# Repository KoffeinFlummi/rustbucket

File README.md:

rustbucket
==========

Access your car's diagnostics via the OBD2 connector with a BeagleBone Blue and Rust (and maybe some MOSFETs). This was inspired by [Marcelo Sacchetin's post about using the BeagleBone Blue's integrated CAN bus transceiver](https://medium.com/bugbountywriteup/car-hacking-with-python-part-1-data-exfiltration-gps-and-obdii-can-bus-69bc6b101fd1). If you want to read the diagnostics for older vehicles, things are a bit more complicated than that. For older VWs for instance, you will need to talk to the vehicle's K line using the KWP1281 protocol. This requires additional hardware to convert the BeagleBone's 3.3V logic level to 12V.

This was developed on/for the BeagleBone Blue, but the K & L line protocols should be just as usable on a BeagleBone Black. As far as I know, accessing the CAN bus on the Black requires the addition of a CAN transceiver.

<p align="center">
    
</p>

# Disclaimer

Hooking stuff up to your vehicle's OBD2 connector can lead to anything from blown fuses to broken hardware. There are [reports online of attempting to communicate with certain VW airbag controllers via KWP1281 bricking them](https://www.ross-tech.com/vag-com/vw_issues.html). There are also apparently [instances of clearing the fault codes using KWP1281 leading to deployed airbags for certain errors](http://wiki.ross-tech.com/wiki/index.php/01217).

I have tested the software and hardware described here successfully on some vehicles/ECUs (see below). However, **I cannot provide any guarantee that using this will not cause permanent damage to you or your vehicle. Proceed at your own risk. Also, don't fuck with airbags please.**

# Protocols

<p align="center">
    
</p>

| Protocol            | Used Lines         | Implemented | Notes |
|---------------------|--------------------|:-----------:|----------------------------------------------------------------------|
| CAN Bus / ISO 15765 | CAN High & CAN Low | ✓           | Used by almost any modern vehicle. No additional hardware needed; The BB Blue's CAN transceiver can be connected directly to the OBD port's CAN lines. |
| KWP1281             | K Line             | ✓           | Not an official OBD2 protocol, used on older VAG (VW & friends) cars. Returned codes are not official OBD2 DTCs. |
| ISO 9141            | K & L Line         | ✗           | Apparently similar to KWP1281, but an official OBD2 protocol. Not implemented, but technically supported by hardware described below. |
| KWP2000 / ISO 14230 | K & L Line         | (✓)         | Implemented at least partially (K line init only, no fast init). OBD2 commands not implemented, but some VAG specific stuff has been tested (see below). |

There are some more OBD2 protocols, that apparently are mostly used on American vehicles. I have not considered these, and the hardware required seems quite different.

Note that the above is my understanding, this whole field is a giant mess of standards and acronyms.

# Features

- Read Diagnostic Trouble Codes, stored and pending
- Clear Diagnostic Trouble Codes
- Read diagnostic data, current and from freeze frame
- Log diagnostic data to CSV for plotting
- Read and write adaptation values, e.g. to reset the service interval (KWP1281 only, no login functionality _yet_)
- Perform basic settings, such as throttle body alignments (KWP1281 only)

# Tested Vehicles/ECUs

| Vehicle/ECU                  | Protocol | Baud/Bit Rate   | Notes |
|------------------------------|----------|-----------------|-------|
| VW Golf Mk4 (1J), 2001       | KWP1281  | 10400,9600,1200 | All ECUs except ESP and airbag controller. See [script](https://github.com/KoffeinFlummi/rustbucket/blob/master/scan_golf_mk4.sh) and [sample output](https://github.com/KoffeinFlummi/rustbucket/blob/master/scan_golf_mk4_sample.out). |
| VW Golf Mk4 (1J), 2001       | KWP2000  | 10400           | ESP Mk60 controller. Reading & clearing DTCs only. |
| VW Golf Mk7 (AUV), 2014      | CAN      | 500000          | Most things work, but multi-frame messages (VIN, more than 2 DTCs) do not. Might require modifications to flow control messages. |
| ~Renault Zoe (AGVYB0), 2015~ | CAN      | 500000          | CAN bus is active, but does not respond to OBD2 queries. I did not spend much time on this, might require some sort of initialization. |
| Siemens SIMOS2.1B ECU        | KWP1281  | 9600            | [Pinout](https://wiki.obdtuning.de/images/9/99/VAG_Simos2.4.jpg) (also has a 500kbps CAN bus on pins 29 (L) & 31 (H), but this is not used for diagnostics and does not respond to OBD2 queries) |
| Bosch EDC16U34 ECU           | CAN      | 500000          | [Pinout](http://diagprof.com/de/ecu_tipps_und_tricks/vag/motorelektronik/bosch/edc16u34) |

# Compiling & Usage

You can compile this directly on the BeagleBone, but the compilation times can be annoying, so the project is set up for cross-compilation. You will have to add the `armv7-unknown-linux-gnueabihf` target using `rustup` (You'll also need a version of GCC compiled for `arm-linux-gnueabihf` for linking. Consult your OS' package manager.):

```
$ rustup target add armv7-unknown-linux-gnueabihf
$ cargo build --release
```

Then, copy the executable to the BeagleBone.

See `rustbucket -h` for usage.

# Testing

The program contains modes for testing the hardware and simulating a car so you can test your hardware using two BeagleBones instead of a car. However, the best way to test is to get yourself a used ECU off of eBay. These can be bought relatively cheaply for older cars (I paid less than 20€ for each of the ECUs I tested with). See references below for some ECU pinouts.

<p align="center">
    
</p>

When testing the CAN protocol with two BeagleBone Blues, you should add a terminating resistor (I used 100Ω) between the CAN lines. The R104 120Ω terminating resistor is not populated from the factory on the BB Blue, and with an unterminated CAN bus you will have problems with the higher bit rates (such as the default 500kbps). This may also apply to some desktop ECUs, but the ones I tested with had 66Ω internal resistors.

# Hardware

For the CAN bus, you can simply connect the BeagleBone Blue's CAN lines directly to the OBD2 connector (On the BeagleBone Black, you'll have to connect a CAN transceiver). For the K Line, the 3.3V logic level of the BeagleBone's UART1 bus will have to be converted to the 12V used on the K line, and vice versa.

I tried to implement [this](https://cdn-shop.adafruit.com/datasheets/an97055.pdf) design for a bi-directional logic level converter using a single N-channel MOSFET, but I couldn't figure out how to do so while making sure that the BeagleBone pins don't sink too much current. Since I had a bunch of N-channel MOSFETs lying around anyway, I just went with this horrendously inefficient design using 2 MOSFETs for reading and writing respectively:

<p align="center">
    
</p>

The BeagleBone's UART1 bus (TX: P9.24, RX: P9.26) is used for writing and reading the K line. The schematic also includes the same setup for writing to the L line, but this is not used in software ATM. Q3 has a gate voltage of 12V, the rest is 3.3V.

If you actually know what you're doing electronics-wise, you can probably come up with something better/more efficient. Contributions appreciated.

I used an IRFZ24NPbF for Q3 and IRLB8748PbF for the others since I had them around. If you're buying components specifically for this there are probably better options, and you may want to go with SMD stuff (or just a better design in general). If you are using TO-220 (G-D-S) components like I did, you may also find the terrible PCB I designed useful. I also have some left over, so let me know if you want one.

KiCAD project (schematic + PCB + Gerber files) can be found [here](https://github.com/KoffeinFlummi/rustbucket/tree/master/kicad).

# References

- Marcelo Sacchetin's post on accessing the CAN Bus with the BeagleBone: https://medium.com/bugbountywriteup/car-hacking-with-python-part-1-data-exfiltration-gps-and-obdii-can-bus-69bc6b101fd1
- Description of KWP1281 protocol (German): https://www.blafusel.de/obd/obd2_kw1281.html (The author mentions that the ECU will report at most 4 DTCs per message. I have received up to 7 DTCs in a single message. Not sure what the upper limit is.)
- List of KWP1281 block titles/types: http://nefariousmotorsports.com/forum/index.php?topic=8274.0title=
- Description of KWP2000 initialization (German): https://www.blafusel.de/obd/vag_kw2000.html
- List of vehicles and their protocol (does not differentiate between the K/KL line protocols): https://www.blafusel.de/obd/vag_compatibility.html
- List of successfully scanned vehicles (German, user-reported and therefore unreliable, but extensive): https://www.blafusel.de/obd/obd2_scanned.php
- List of Fault Codes, including pre-OBD VAG ones: http://wiki.ross-tech.com/wiki/index.php?title=Category:Fault_Codes
- List of ECUs and their pinouts (German, useful for hooking up ECU directly): https://wiki.obdtuning.de/index.php?title=Hauptseite
- More ECU pinouts: http://diagprof.com/ecu_tips_and_tricks/manufacturer-vag/ecudomain-pcm_powertrain_control_module/supplier-bosch
- Some nice examples of CAN bus issues: https://www.kvaser.com/about-can/the-can-protocol/can-oscilloscope-pictures/

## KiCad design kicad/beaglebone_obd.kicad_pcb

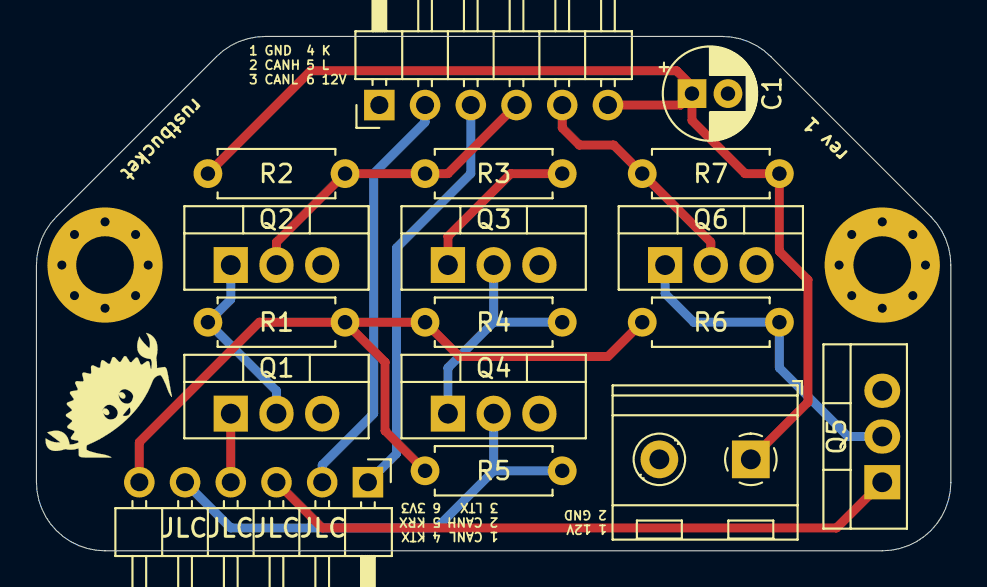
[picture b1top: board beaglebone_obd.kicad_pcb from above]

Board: 2 copper layers, 50.8 x 28.6 mm, 14 parts (0 on the bottom side), 10 nets.

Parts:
C1: 47u; CP_Radial_D5.0mm_P2.00mm
Q1, Q2, Q3, Q4, Q5, Q6: IRLB8721PBF; TO-220-3_Vertical
R1, R2, R4, R5, R6, R7: 1K; R_Axial_DIN0207_L6.3mm_D2.5mm_P7.62mm_Horizontal
R3: 10K; R_Axial_DIN0207_L6.3mm_D2.5mm_P7.62mm_Horizontal

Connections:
+3V3: R1.1, R4.1, R5.1, R6.1
+12V: C1.1, R2.1, R7.1
GND: C1.2, Q1.3, Q2.3, Q3.3, Q4.3, Q5.3, Q6.3
K: Q2.2, R2.2, R3.1
KRX: Q4.2, R5.2
L: Q6.2, R7.2
unnamed: Q1.2, Q2.1, R1.2
unnamed: Q3.1, R3.2
unnamed: Q3.2, Q4.1, R4.2
unnamed: Q5.2, Q6.1, R6.2

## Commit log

2020-09-09 Add Golf 4 test picture
2020-09-11 Add linker hint to README.
2020-09-11 Add data reading, refactor main.rs
2020-09-11 Add lib.rs, missing docs
2020-09-11 Make minor doc changes
2020-09-11 Add OBD2 data parsing
2020-09-11 cargo fmt
2020-09-11 Make raw hex dump non-default
2020-09-12 Make minor README and output changes
2020-09-12 Handle 1 byte oxygen sensor trim messages
2020-09-12 Continue after VIN failure
2020-09-12 Add test data
2020-09-29 Refactor data reading, add CSV logging
    I'm not very happy with the way the data parsing works, but it will do
    for now.
2020-09-29 Add formula for lambda values
2020-09-29 Add Python script for plotting logged data
2020-09-29 Rename dtc.rs
2020-09-29 Allow talking to other ECUs, add adaptation cmd
2020-11-10 Reset pin modes on failure
2020-11-10 Add more baud rates
    Golf Mk4 automatic transmission needed 1200 baud
2020-11-10 Always print key bytes during KWP1281 init
2020-11-10 Add KWP2000 implementation for VAG specific stuff
    Removes the OBD2 stuff for KWP2000 for now, but that was untested
    anyways. KWP2000 stuff was tested on ESP Mk60 controller, may not
    immediately work for other ECUs.
2020-11-10 Add sample script and output for Golf Mk4
2020-11-10 Update README.md with KWP2000 and Golf Mk4 script
2020-11-10 Add KWP1281 basic setting support
2020-11-10 Fix typo
